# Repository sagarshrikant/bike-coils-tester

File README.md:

# SPARKBENCH

**Pickup · CDI · coil tester for motorcycles.** (Repo name: bike-coils-tester.)

A bench tester for motorcycle **pickup coils**, **AC/DC CDI units** and **ignition coils**. It tests
each part on its own, or the whole chain from pickup to spark, and reports which part failed.
It's built around a Raspberry Pi Pico W and a Flutter app (Android / iOS / Web) over Wi-Fi.

> ⚠️ Ignition systems produce lethal voltages. Read [docs/safety.md](docs/safety.md) first.

| Start here | |
|---|---|
| [docs/test-plan.md](docs/test-plan.md) | What gets tested and how, with pass/fail criteria |
| [docs/architecture.md](docs/architecture.md) | Channels, pin map, API |
| [docs/roadmap.md](docs/roadmap.md) | Phases; current = **Phase 1: Wi-Fi + resistance** |
| [hardware/circuits/ch-r2-resistance.md](hardware/circuits/ch-r2-resistance.md) | Phase 1 circuit to build on perfboard |
| [hardware/bom.md](hardware/bom.md) | Parts list |
| [firmware/README.md](firmware/README.md) | Flash and deploy the Pico W |
| [app/README.md](app/README.md) | Set up and run the Flutter app |

Diagrams (`hardware/diagrams/*.drawio.svg`) open directly in draw.io for editing.

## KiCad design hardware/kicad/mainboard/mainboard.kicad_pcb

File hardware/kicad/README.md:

# KiCad project: mainboard

Project: `hardware/kicad/mainboard/mainboard.kicad_pro` (schematic `mainboard.kicad_sch`, board `mainboard.kicad_pcb`).
The files KiCad writes (`.kicad_pro`, `.kicad_sch`, `.kicad_pcb`) are text and belong in git. Backups and caches are ignored (see `.gitignore`).

## Library setup (the AppImage ships without the standard libraries)

Close KiCad, then in a terminal (matching tag 10.0.8, adjust it if your KiCad version differs):

```bash
mkdir -p ~/kicad-libs && cd ~/kicad-libs
git clone --depth 1 --branch 10.0.8 https://gitlab.com/kicad/libraries/kicad-symbols.git
git clone --depth 1 --branch 10.0.8 https://gitlab.com/kicad/libraries/kicad-footprints.git
cd ~/personal/projects/bike-coils-tester      # the repo folder on your computer
bash tools/kicad/make-lib-tables.sh
```

The script copies the library tables that ship with the libraries (they use path variables) into KiCad's config folder and writes the real
folders into them. It backs up any existing tables. (KiCad 10 stores each symbol library as a `.kicad_symdir` folder, not a single file.) The 3D model library is
very large and is not needed for the circuit or the board; skip it for now.

### Parts worth knowing in the standard libraries (checked in the 10.0.8 libraries)

| Part | Symbol | Footprint |
|---|---|---|
| Pico 2 W | `MCU_Module:RaspberryPi_Pico_W` (same pin layout; it inherits its pins from `RaspberryPi_Pico`) | `Module:RaspberryPi_Pico_Common_THT` (the pads for the two 1×20 sockets) |
| MCP23017 (SPDIP-28) | `Interface_Expansion:MCP23017x-x-SP` | DIP-28 narrow from `Package_DIP` |
| ADS1115 | `Analog_ADC:ADS1115IDGS` | VSSOP-10 from `Package_SO` |
| Resistor, capacitor | `Device:R`, `Device:C` | `Resistor_SMD:R_0805_2012Metric`, `Capacitor_SMD:C_0805_2012Metric` |
| Connector 1×N | `Connector_Generic:Conn_01x20` etc. | `Connector_PinSocket_2.54mm` / `TerminalBlock` |

## Source of truth for the drawing

| What | Where |
|---|---|
| Overview, Pico pins, expanders, connectors, test points | `hardware/circuits/mainboard.md` and `hardware/diagrams/mainboard-schematic.drawio.svg` |
| CH-R2 | `hardware/circuits/ch-r2-pcb.md` + `ch-r2-ads1115-schematic.drawio.svg` |
| CH-PU | `hardware/circuits/ch-pu-pickup.md` + `ch-pu-schematic.drawio.svg` |
| ARM stage and 12 V input | `hardware/circuits/power-arm.md` + `power-arm-schematic.drawio.svg` |
| CH-TG | `hardware/circuits/ch-tg-trigger.md` + `ch-tg-schematic.drawio.svg` |
| Parts and quantities | `hardware/bom-order-list.xlsx` |
| Pin map | `docs/pin-budget.md` |

## Suggested structure

- **Root sheet** = mainboard: Pico socket, the two MCP23017, the I²C bus, the connectors, test points.
- **One hierarchical sheet per block:** `ch_r2`, `ch_pu`, `arm`, `ch_tg`. Sheet pins carry the net names used in the docs.
- Use the **same net names as the docs** (`SDA`, `PU_SIG`, `12V_ARMED`, `MUX_A`, ...). Nets with the same name on one sheet are connected, so net labels are fine.
- Two grounds: **GND_L** and **GND_P**, with different net names, joined nowhere. Use a different ground symbol or name for each (for example `GND` for GND_L and `GNDP` for GND_P).
- Fill in the **Value** and **Footprint** fields from the order list. Add an **MPN** field with the part number you will actually buy.
- Run **ERC** and fix every error; do not just silence them.

## PCB checklist

- 2 layers, 1.6 mm. Board outline about 100 × 120 mm, 4 × M3 holes.
- **Isolation slot** of at least 2 mm between the logic and the 12 V regions: draw it on the board outline layer (Edge.Cuts) as a routed slot, with no copper crossing it. Only the optocouplers, photoMOS relays and the ADuM1250 span it.
- 12V_RAW / 12V_ARMED traces about 2.5 mm wide, or pours.
- Decoupling capacitors right at each IC supply pin.
- Footprints match the real parts (relay pin spacing, TO-92 pin order, terminal pitch 5.08 mm, SOIC-16, VSSOP-10).
- Run **DRC**, then check the 3D view.
- Export: PDF of the schematic, PNG/PDF of the layout, then Gerbers and drill files to `hardware/kicad/mainboard/fab/` (ignored by git).

## Generated sheets (netlist-style, every pin labelled)

| File | Content | Generator |
|---|---|---|
| `mainboard/mainboard-io.kicad_sch` | Pico, 2 × MCP23017, ADS1115 module headers, bus pull-ups, expander pull resistors, reset button, J8 | `KICAD_SYMBOLS=<kicad-symbols checkout> node tools/kicad/gen-io-sheet.mjs` |
| `mainboard/mainboard-ch-tg.kicad_sch` | CH-TG: supplies (78L05, 3.3 V LDO, ICL7660, 78L09), ADuM1250, DACs + TL072, 4052 mux, JP1, optocouplers, photoMOS bank, J5, TVS, measurement dividers (paper A2) | `KICAD_SYMBOLS=<kicad-symbols checkout> node tools/kicad/gen-ch-tg-sheet.mjs` |
| `mainboard/mainboard-ch-pu.kicad_sch` | CH-PU pickup input (TVS, loads, R_INJ, divider, 74HC4066 legs, clamp header JC2, buffers, bias, DAC, comparators, optional peak hold DNP) | `KICAD_SYMBOLS=<kicad-symbols checkout> node tools/kicad/gen-ch-pu-sheet.mjs` |
| `mainboard/mainboard-ch-r2.kicad_sch` | CH-R2 resistance meter (R_REF, filters, clamp header JC1, TVS, self-test photoMOS, 3V3A filter, AGND tie) | `KICAD_SYMBOLS=<kicad-symbols checkout> node tools/kicad/gen-ch-r2-sheet.mjs` |
| `mainboard/mainboard-arm.kicad_sch` | 12 V input, Q1/Q2, relay K1, sense optocouplers, outputs | `KICAD_SYMBOLS=<kicad-symbols checkout> node tools/kicad/gen-arm-sheet.mjs` (add `--nets` to print the net list) |

Add them with Place → Add sheet. The global labels connect the sheets (PWR_EN, RLY_EN, MID_SENSE, ARM_SENSE, 3V3, GND_L).
Do not edit the labels by hand: change the generator, regenerate, and tell me.

Cross-sheet check: `node tools/kicad/check-labels.mjs` (lists labels that connect to nothing). Review points for each sheet: `review-checklist.md`.

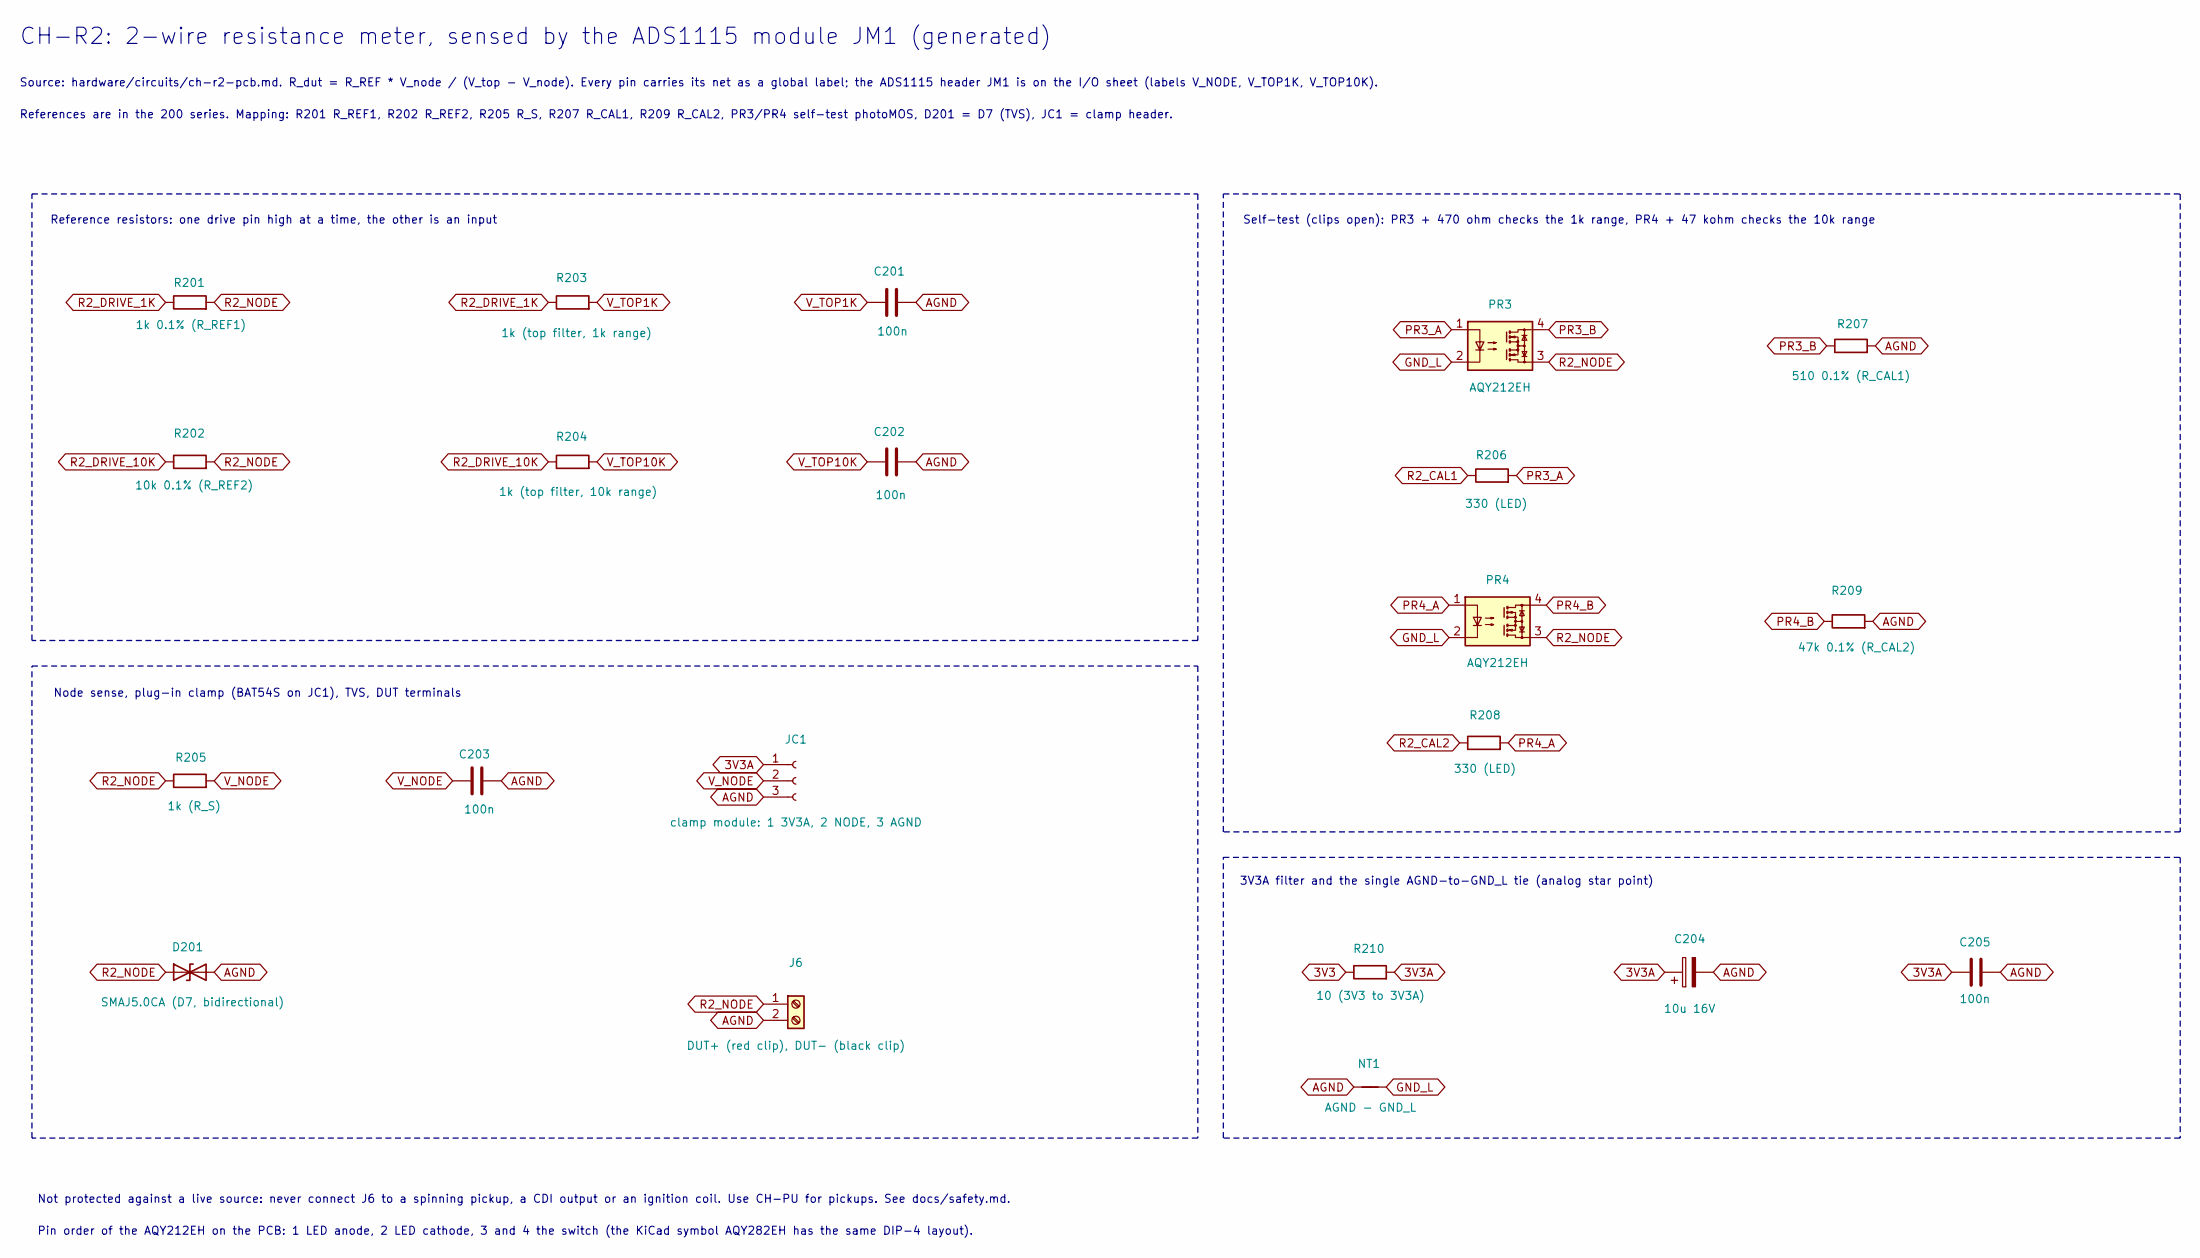
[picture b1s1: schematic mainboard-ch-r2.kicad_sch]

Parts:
C201, C202, C203, C205: 100n; C_0805_2012Metric
C204: 10u 16V; C_0805_2012Metric
D201: SMAJ5.0CA (D7, bidirectional); D_SMA
J6: DUT+ (red clip), DUT- (black clip); TerminalBlock_Phoenix_MKDS-1,5-2-5.08_1x02_P5.08mm_Horizont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
JC1: clamp module: 1 3V3A, 2 NODE, 3 AGND; PinSocket_1x03_P2.54mm_Vertical
NT1: AGND - GND_L; NetTie-2_SMD_Pad0.5mm
PR3, PR4: AQY212EH; DIP-4_W7.62mm
R201: 1k 0.1% (R_REF1); R_0805_2012Metric
R202: 10k 0.1% (R_REF2); R_0805_2012Metric
R203: 1k (top filter, 1k range); R_0805_2012Metric
R204: 1k (top filter, 10k range); R_0805_2012Metric
R205: 1k (R_S); R_0805_2012Metric
R206, R208: 330 (LED); R_0805_2012Metric
R207: 510 0.1% (R_CAL1); R_0805_2012Metric
R209: 47k 0.1% (R_CAL2); R_0805_2012Metric
R210: 10 (3V3 to 3V3A); R_0805_2012Metric

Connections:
3V3: R210.1; also elsewhere on the board
3V3A: C204.1, C205.1, JC1.1, R210.2; also elsewhere on the board
AGND: C201.2, C202.2, C203.2, C204.2, C205.2, D201.2 (A2), J6.2, JC1.3, NT1.1, R207.2, R209.2; also elsewhere on the board
GND_L: NT1.2, PR3.2, PR4.2; also elsewhere on the board
PR3_A: PR3.1, R206.2
PR3_B: PR3.4, R207.1
PR4_A: PR4.1, R208.2
PR4_B: PR4.4, R209.1
R2_CAL1: R206.1; also elsewhere on the board
R2_CAL2: R208.1; also elsewhere on the board
R2_DRIVE_1K: R201.1, R203.1; also elsewhere on the board
R2_DRIVE_10K: R202.1, R204.1; also elsewhere on the board
R2_NODE: D201.1 (A1), J6.1, PR3.3, PR4.3, R201.2, R202.2, R205.1
V_NODE: C203.1, JC1.2, R205.2; also elsewhere on the board
V_TOP1K: C201.1, R203.2; also elsewhere on the board
V_TOP10K: C202.1, R204.2; also elsewhere on the board

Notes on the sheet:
Self-test (clips open): PR3 + 470 ohm checks the 1k range, PR4 + 47 kohm checks the 10k range
Not protected against a live source: never connect J6 to a spinning pickup, a CDI output or an ignition coil. Use CH-PU for pickups. See docs/safety.md.
CH-R2: 2-wire resistance meter, sensed by the ADS1115 module JM1 (generated)
References are in the 200 series. Mapping: R201 R_REF1, R202 R_REF2, R205 R_S, R207 R_CAL1, R209 R_CAL2, PR3/PR4 self-test photoMOS, D201 = D7 (TVS), JC1 = clamp header.
Reference resistors: one drive pin high at a time, the other is an input
Source: hardware/circuits/ch-r2-pcb.md. R_dut = R_REF * V_node / (V_top - V_node). Every pin carries its net as a global label; the ADS1115 header JM1 is on the I/O sheet (labels V_NODE, V_TOP1K, V_TOP10K).
Node sense, plug-in clamp (BAT54S on JC1), TVS, DUT terminals
Pin order of the AQY212EH on the PCB: 1 LED anode, 2 LED cathode, 3 and 4 the switch (the KiCad symbol AQY282EH has the same DIP-4 layout).
3V3A filter and the single AGND-to-GND_L tie (analog star point)

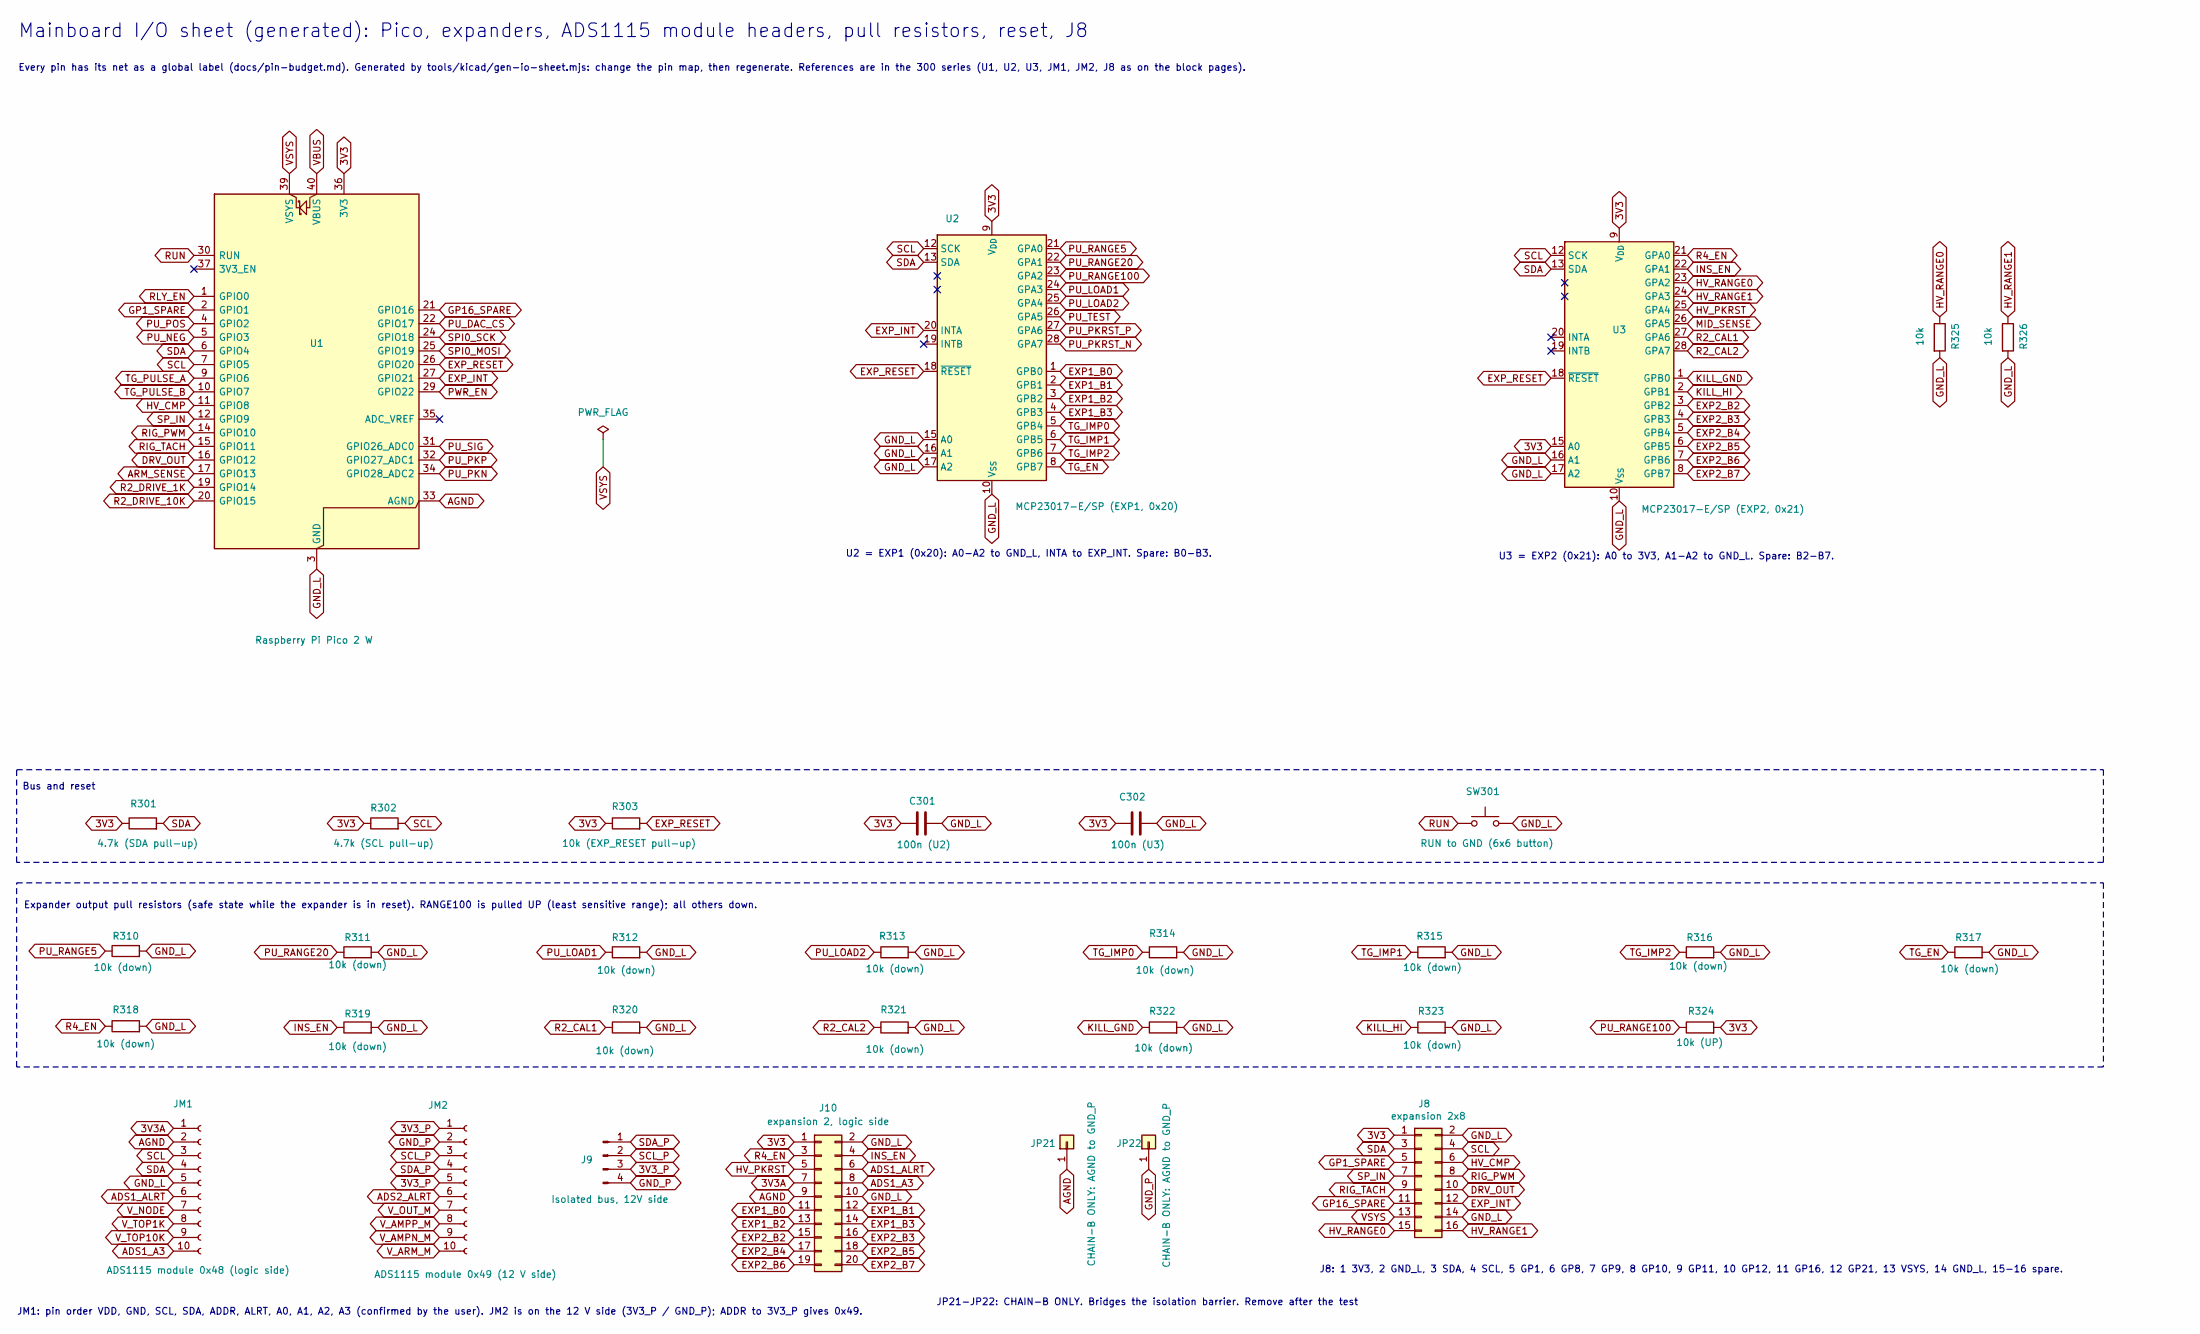
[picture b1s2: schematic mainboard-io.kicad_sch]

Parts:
C301: 100n (U2); C_0805_2012Metric
C302: 100n (U3); C_0805_2012Metric
J8: expansion 2x8; PinHeader_2x08_P2.54mm_Vertical
J9: Isolated bus, 12V side; PinHeader_1x04_P2.54mm_Vertical
J10: expansion 2, logic side; PinHeader_2x10_P2.54mm_Vertical
JM1: ADS1115 module 0x48 (logic side); PinSocket_1x10_P2.54mm_Vertical
JM2: ADS1115 module 0x49 (12 V side); PinSocket_1x10_P2.54mm_Vertical
JP21, JP22: CHAIN-B ONLY: AGND to GND_P; PinHeader_1x01_P2.54mm_Vertical
R301: 4.7k (SDA pull-up); R_0805_2012Metric
R302: 4.7k (SCL pull-up); R_0805_2012Metric
R303: 10k (EXP_RESET pull-up); R_0805_2012Metric
R310, R311, R312, R313, R314, R315, R316, R317, R318, R319, R320, R321, R322, R323: 10k (down); R_0805_2012Metric
R324: 10k (UP); R_0805_2012Metric
R325, R326: 10k; R_0805_2012Metric
SW301: RUN to GND (6x6 button); SW_PUSH_6mm
U1: Raspberry Pi Pico 2 W; RaspberryPi_Pico_Common_THT
U2: MCP23017-E/SP (EXP1, 0x20); DIP-28_W7.62mm
U3: MCP23017-E/SP (EXP2, 0x21); DIP-28_W7.62mm

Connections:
3V3: C301.1, C302.1, J8.1, J10.1, R301.1, R302.1, R303.1, R324.2, U1.36 (3V3), U2.9 (V_{DD}), U3.9 (V_{DD}), U3.15 (A0); also elsewhere on the board
3V3A: J10.7, JM1.1; also elsewhere on the board
3V3_P: J9.3, JM2.1, JM2.5; also elsewhere on the board
ADS1_A3: J10.8, JM1.10
ADS1_ALRT: J10.6, JM1.6
ADS2_ALRT: JM2.6
AGND: J10.9, JM1.2, JP21.1 (Pin_1_1), U1.33 (AGND); also elsewhere on the board
ARM_SENSE: U1.17 (GPIO13); also elsewhere on the board
DRV_OUT: J8.10, U1.16 (GPIO12)
EXP1_B0: J10.11, U2.1 (GPB0)
EXP1_B1: J10.12, U2.2 (GPB1)
EXP1_B2: J10.13, U2.3 (GPB2)
EXP1_B3: J10.14, U2.4 (GPB3)
EXP2_B2: J10.15, U3.3 (GPB2)
EXP2_B3: J10.16, U3.4 (GPB3)
EXP2_B4: J10.17, U3.5 (GPB4)
EXP2_B5: J10.18, U3.6 (GPB5)
EXP2_B6: J10.19, U3.7 (GPB6)
EXP2_B7: J10.20, U3.8 (GPB7)
EXP_INT: J8.12, U1.27 (GPIO21), U2.20 (INTA)
EXP_RESET: R303.2, U1.26 (GPIO20), U2.18 (~RESET), U3.18 (~RESET)
GND_L: C301.2, C302.2, J8.2, J8.14, J10.2, J10.10, JM1.5, R310.2, R311.2, R312.2, R313.2, R314.2, R315.2, R316.2, R317.2, R318.2, R319.2, R320.2, R321.2, R322.2, R323.2, R325.2, R326.2, SW301.2, U1.3 (GND), U1.8 (GND), U1.13 (GND), U1.18 (GND), U1.23 (GND), U1.28 (GND), U1.38 (GND), U2.10 (V_{SS}), U2.15 (A0), U2.16 (A1), U2.17 (A2), U3.10 (V_{SS}), U3.16 (A1), U3.17 (A2); also elsewhere on the board
GND_P: J9.4, JM2.2, JP22.1 (Pin_1_1); also elsewhere on the board
GP1_SPARE: J8.5, U1.2 (GPIO1)
GP16_SPARE: J8.11, U1.21 (GPIO16)
HV_CMP: J8.6, U1.11 (GPIO8)
HV_PKRST: J10.5, U3.25 (GPA4)
HV_RANGE0: J8.15, R325.1, U3.23 (GPA2)
HV_RANGE1: J8.16, R326.1, U3.24 (GPA3)
INS_EN: J10.4, R319.1, U3.22 (GPA1)
KILL_GND: R322.1, U3.1 (GPB0); also elsewhere on the board
KILL_HI: R323.1, U3.2 (GPB1); also elsewhere on the board
MID_SENSE: U3.26 (GPA5); also elsewhere on the board
PU_DAC_CS: U1.22 (GPIO17); also elsewhere on the board
PU_LOAD1: R312.1, U2.24 (GPA3); also elsewhere on the board
PU_LOAD2: R313.1, U2.25 (GPA4); also elsewhere on the board
PU_NEG: U1.5 (GPIO3); also elsewhere on the board
PU_PKN: U1.34 (GPIO28_ADC2); also elsewhere on the board
PU_PKP: U1.32 (GPIO27_ADC1); also elsewhere on the board
PU_PKRST_N: U2.28 (GPA7); also elsewhere on the board
PU_PKRST_P: U2.27 (GPA6); also elsewhere on the board
PU_POS: U1.4 (GPIO2); also elsewhere on the board
PU_RANGE5: R310.1, U2.21 (GPA0); also elsewhere on the board
PU_RANGE20: R311.1, U2.22 (GPA1); also elsewhere on the board
PU_RANGE100: R324.1, U2.23 (GPA2); also elsewhere on the board
PU_SIG: U1.31 (GPIO26_ADC0); also elsewhere on the board
PU_TEST: U2.26 (GPA5); also elsewhere on the board
PWR_EN: U1.29 (GPIO22); also elsewhere on the board
R2_CAL1: R320.1, U3.27 (GPA6); also elsewhere on the board
R2_CAL2: R321.1, U3.28 (GPA7); also elsewhere on the board
R2_DRIVE_1K: U1.19 (GPIO14); also elsewhere on the board
R2_DRIVE_10K: U1.20 (GPIO15); also elsewhere on the board
R4_EN: J10.3, R318.1, U3.21 (GPA0)
RIG_PWM: J8.8, U1.14 (GPIO10)
RIG_TACH: J8.9, U1.15 (GPIO11)
RLY_EN: U1.1 (GPIO0); also elsewhere on the board
RUN: SW301.1, U1.30 (RUN)
SCL: J8.4, JM1.3, R302.2, U1.7 (GPIO5), U2.12 (SCK), U3.12 (SCK); also elsewhere on the board
SCL_P: J9.2, JM2.3; also elsewhere on the board
SDA: J8.3, JM1.4, R301.2, U1.6 (GPIO4), U2.13 (SDA), U3.13 (SDA); also elsewhere on the board
SDA_P: J9.1, JM2.4; also elsewhere on the board
SPI0_MOSI: U1.25 (GPIO19); also elsewhere on the board
SPI0_SCK: U1.24 (GPIO18); also elsewhere on the board
SP_IN: J8.7, U1.12 (GPIO9)
TG_EN: R317.1, U2.8 (GPB7); also elsewhere on the board
TG_IMP0: R314.1, U2.5 (GPB4); also elsewhere on the board
TG_IMP1: R315.1, U2.6 (GPB5); also elsewhere on the board
TG_IMP2: R316.1, U2.7 (GPB6); also elsewhere on the board
TG_PULSE_A: U1.9 (GPIO6); also elsewhere on the board
TG_PULSE_B: U1.10 (GPIO7); also elsewhere on the board
VBUS: U1.40 (VBUS)
VSYS: J8.13, U1.39 (VSYS)
V_AMPN_M: JM2.9; also elsewhere on the board
V_AMPP_M: JM2.8; also elsewhere on the board
V_ARM_M: JM2.10; also elsewhere on the board
V_NODE: JM1.7; also elsewhere on the board
V_OUT_M: JM2.7; also elsewhere on the board
V_TOP1K: JM1.8; also elsewhere on the board
V_TOP10K: JM1.9; also elsewhere on the board

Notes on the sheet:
Expander output pull resistors (safe state while the expander is in reset). RANGE100 is pulled UP (least sensitive range); all others down.
Bus and reset
U2 = EXP1 (0x20): A0-A2 to GND_L, INTA to EXP_INT. Spare: B0-B3.
Every pin has its net as a global label (docs/pin-budget.md). Generated by tools/kicad/gen-io-sheet.mjs: change the pin map, then regenerate. References are in the 300 series (U1, U2, U3, JM1, JM2, J8 as on the block pages).
JM1: pin order VDD, GND, SCL, SDA, ADDR, ALRT, A0, A1, A2, A3 (confirmed by the user). JM2 is on the 12 V side (3V3_P / GND_P); ADDR to 3V3_P gives 0x49.
Mainboard I/O sheet (generated): Pico, expanders, ADS1115 module headers, pull resistors, reset, J8
JP21-JP22: CHAIN-B ONLY. Bridges the isolation barrier. Remove after the test
U3 = EXP2 (0x21): A0 to 3V3, A1-A2 to GND_L. Spare: B2-B7.
J8: 1 3V3, 2 GND_L, 3 SDA, 4 SCL, 5 GP1, 6 GP8, 7 GP9, 8 GP10, 9 GP11, 10 GP12, 11 GP16, 12 GP21, 13 VSYS, 14 GND_L, 15-16 spare.
